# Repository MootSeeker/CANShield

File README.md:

# CANShield

STM32 Nucleo-64 Development Shield to connect NXP TJA1443 CANbus chip with some memory and GPS probe interface.

## Table of Contents
- [About](#about)
- [Features](#features)
- [Circuit Description](#circuit-description)
- [Hardware Requirements](#hardware-requirements)
- [Installation](#installation)
- [Usage](#usage)
- [Contributing](#contributing)
- [License](#license)
- [Contact](#contact)

## About
CANShield is a development shield designed for the STM32 Nucleo-64 board. It integrates an NXP TJA1443 CANbus transceiver, additional memory, and a GPS probe interface to facilitate the development and testing of CANbus applications. This shield provides a versatile and powerful platform for engineers and developers working on CANbus networks and applications, offering the tools needed to prototype and experiment with CAN-FD protocols.

## Features
- **Compatibility**: Fully compatible with STM32 Nucleo-64 boards, providing a seamless integration experience.
- **NXP TJA1443 CANbus Transceiver**: High-speed CAN-FD transceiver for robust and reliable CANbus communication.
- **Integrated Memory**: Additional memory for data storage, enabling complex applications and logging capabilities.
- **GPS Probe Interface**: Easy integration with GPS modules for applications requiring location data.
- **KiCad Design Files**: Open-source design files available, allowing for easy modifications and customizations.

## Circuit Description
This project includes the development and implementation of a custom development board with the NXP TJA1443 CAN-FD chip. The board connects to an Nucleo-64 development board, specifically the Nucleo-32G0B1, to fully exploit the capabilities of the CAN-FD interface.

The main purpose of this project is to utilize the full potential of the NXP TJA1443 chip in a CAN-FD network. By integrating this chip with the Nucleo-32G0B1, we aim to develop and test various protocols within the CAN network, providing a robust platform for CAN-FD communication.

Key Features:
- **NXP TJA1443 CAN-FD Chip**: High-speed CAN transceiver with advanced features for CAN-FD networks.
- **Nucleo-32G0B1 Compatibility**: Utilizes the STM32G0 microcontroller with integrated CAN-FD support.
- **Custom Development Board**: Tailored design for easy integration and testing of CAN-FD protocols.
- **Protocol Development and Testing**: Focus on creating and evaluating various protocols within the CAN network.

This project provides a comprehensive platform for developing and testing CAN-FD protocols, leveraging the capabilities of the NXP TJA1443 chip and the Nucleo-32G0B1 development board.

## Hardware Requirements
To get started with CANShield, you will need the following hardware components:
- **STM32 Nucleo-64 Board**: The main development board that hosts the STM32 microcontroller.
- **CANShield Board**: The custom shield that integrates the NXP TJA1443 CAN-FD transceiver, memory, and GPS interface.
- **GPS Probe (Optional)**: A GPS module for applications requiring geographic data.
- **Power Supply**: Appropriate power supply to power the Nucleo-64 and CANShield boards.

## Installation
1. **Clone the Repository**: Start by cloning the CANShield repository to your local machine.
    ```sh
    git clone https://github.com/MootSeeker/CANShield.git
    ```
2. **Open KiCad Project**: Open the KiCad project files located in the `CANShield` directory to review the schematics and PCB layout.
3. **Assemble the Shield**: Assemble the CANShield board according to the provided schematics and Bill of Materials (BOM). Ensure all components are correctly soldered and connected.
4. **Attach to Nucleo-64**: Connect the assembled CANShield board to the STM32 Nucleo-64 board.

## Usage
1. **Setup Hardware**: Attach the CANShield to the STM32 Nucleo-64 board. Connect the GPS probe to the shield if needed.
2. **Power Up**: Supply power to the setup using an appropriate power source.
3. **Program the STM32**: Upload your CANbus application code to the STM32 microcontroller using your preferred development environment (e.g., STM32CubeIDE).
4. **Monitor Communication**: Use CANbus monitoring tools to observe and debug the communication on the CANbus network. This can be done using software tools or hardware analyzers.

## Contributing
Contributions are welcome! Whether you have suggestions for improvements, bug fixes, or new features, please feel free to contribute. Here’s how you can get involved:
- **Open an Issue**: Report bugs or suggest features by opening an issue on the GitHub repository.
- **Submit a Pull Request**: Fork the repository, make your changes, and submit a pull request for review.
- **Documentation**: Help improve the project documentation by adding examples, tutorials, or clarifications.

## License
This project is licensed under the MIT License. You are free to use, modify, and distribute this project as per the terms of the license. See the [LICENSE](LICENSE) file for more details.

## Contact
For questions, feedback, or more information, please contact [MootSeeker](https://github.com/MootSeeker). We look forward to hearing from you and seeing how you use CANShield in your projects!

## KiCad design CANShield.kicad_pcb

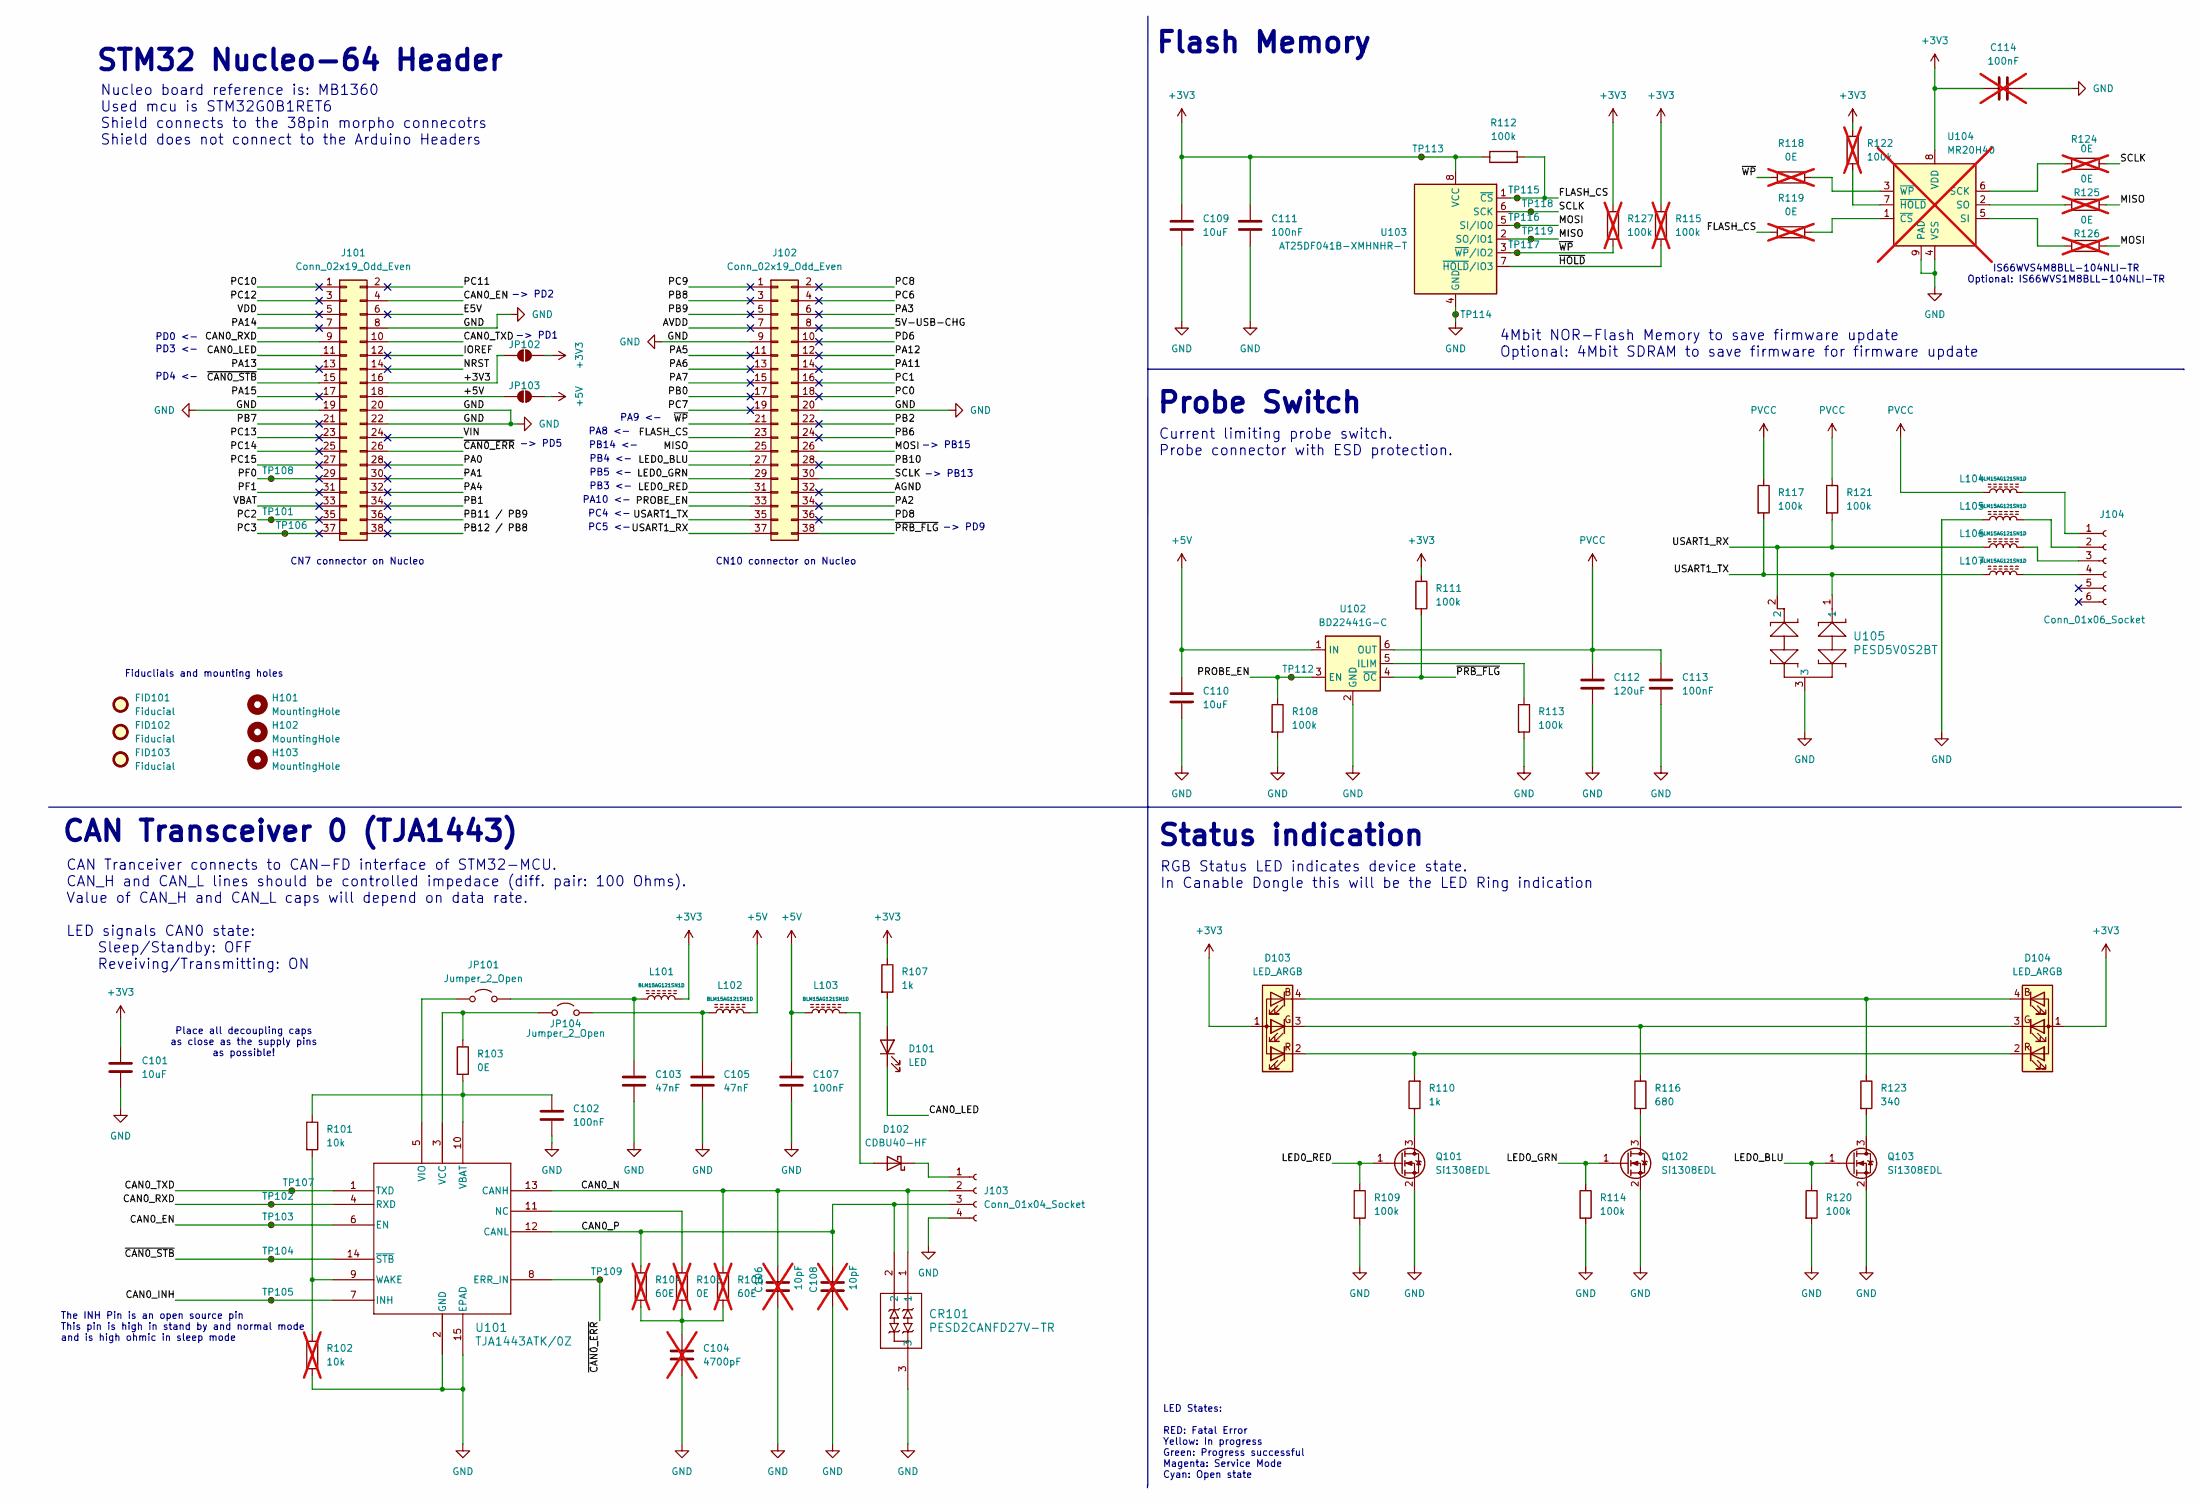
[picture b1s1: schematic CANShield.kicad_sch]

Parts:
C101, C109, C110: 10uF; C_0603_1608Metric_Pad1.08x0.95mm_HandSolder; JLCPCB Part # (optional) ${ITEM_NUMBER}
C102, C107, C111, C113: 100nF; C_0402_1005Metric_Pad0.74x0.62mm_HandSolder; JLCPCB Part # (optional) ${ITEM_NUMBER}
C103, C105: 47nF; C_0402_1005Metric_Pad0.74x0.62mm_HandSolder; JLCPCB Part # (optional) ${ITEM_NUMBER}
C104: 4700pF; C_0402_1005Metric_Pad0.74x0.62mm_HandSolder; JLCPCB Part # (optional) ${ITEM_NUMBER}; not fitted
C106, C108: 10pF; C_0402_1005Metric_Pad0.74x0.62mm_HandSolder; JLCPCB Part # (optional) ${ITEM_NUMBER}; not fitted
C112: 120uF; C_0603_1608Metric_Pad1.08x0.95mm_HandSolder; JLCPCB Part # (optional) ${ITEM_NUMBER}
C114: 100nF; C_0402_1005Metric_Pad0.74x0.62mm_HandSolder; JLCPCB Part # (optional) ${ITEM_NUMBER}; not fitted
CR101: PESD2CANFD27V-TR; SOT23_PESD2_NEX; JLCPCB Part # (optional) ${ITEM_NUMBER}
D101: LED; LED_0402_1005Metric_Pad0.77x0.64mm_HandSolder; JLCPCB Part # (optional) ${ITEM_NUMBER}
D102: CDBU40-HF; D_0603_1608Metric; JLCPCB Part # (optional) ${ITEM_NUMBER}
D103, D104: LED_ARGB; LED_155124M173200; JLCPCB Part # (optional) ${ITEM_NUMBER}
FID101, FID102, FID103: Fiducial; Fiducial_0.75mm_Mask2.25mm; JLCPCB Part # (optional) ${ITEM_NUMBER}
H101, H102, H103: MountingHole; MountingHole_2.7mm_M2.5; JLCPCB Part # (optional) ${ITEM_NUMBER}
J101, J102: Conn_02x19_Odd_Even; PinSocket_2x19_P2.54mm_Vertical; JLCPCB Part # (optional) ${ITEM_NUMBER}
J103: Conn_01x04_Socket; PinHeader_1x04_P2.54mm_Horizontal; JLCPCB Part # (optional) ${ITEM_NUMBER}
J104: Conn_01x06_Socket; Molex_PicoBlade_53048-0610_1x06_P1.25mm_Horizontal; JLCPCB Part # (optional) ${ITEM_NUMBER}
JP101, JP104: Jumper_2_Open; PinHeader_1x02_P2.54mm_Vertical; JLCPCB Part # (optional) ${ITEM_NUMBER}
JP102, JP103: SolderJumper_2_Open; PinHeader_1x02_P2.54mm_Vertical; JLCPCB Part # (optional) ${ITEM_NUMBER}
L101, L102, L103, L104, L105, L106, L107: BLM15AG121SN1D; L_0402_1005Metric_Pad0.77x0.64mm_HandSolder; JLCPCB Part # (optional) ${ITEM_NUMBER}
Q101, Q102, Q103: Si1308EDL; SOT-323_SC-70; JLCPCB Part # (optional) ${ITEM_NUMBER}
R101: 10k; R_0402_1005Metric_Pad0.72x0.64mm_HandSolder; JLCPCB Part # (optional) ${ITEM_NUMBER}
R102: 10k; R_0402_1005Metric_Pad0.72x0.64mm_HandSolder; JLCPCB Part # (optional) ${ITEM_NUMBER}; not fitted
R103: 0E; R_0402_1005Metric_Pad0.72x0.64mm_HandSolder; JLCPCB Part # (optional) ${ITEM_NUMBER}
R104, R106: 60E; R_0603_1608Metric_Pad0.98x0.95mm_HandSolder; JLCPCB Part # (optional) ${ITEM_NUMBER}; not fitted
R105: 0E; R_0603_1608Metric_Pad0.98x0.95mm_HandSolder; JLCPCB Part # (optional) ${ITEM_NUMBER}; not fitted
R107, R110: 1k; R_0402_1005Metric_Pad0.72x0.64mm_HandSolder; JLCPCB Part # (optional) ${ITEM_NUMBER}
R108, R109, R111, R112, R113, R114, R117, R120, R121: 100k; R_0402_1005Metric_Pad0.72x0.64mm_HandSolder; JLCPCB Part # (optional) ${ITEM_NUMBER}
R115, R122, R127: 100k; R_0402_1005Metric_Pad0.72x0.64mm_HandSolder; JLCPCB Part # (optional) ${ITEM_NUMBER}; not fitted
R116: 680; R_0402_1005Metric_Pad0.72x0.64mm_HandSolder; JLCPCB Part # (optional) ${ITEM_NUMBER}
R118, R119, R124, R125, R126: 0E; R_0402_1005Metric_Pad0.72x0.64mm_HandSolder; JLCPCB Part # (optional) ${ITEM_NUMBER}; not fitted
R123: 340; R_0402_1005Metric_Pad0.72x0.64mm_HandSolder; JLCPCB Part # (optional) ${ITEM_NUMBER}
TP101, TP102, TP103, TP104, TP105, TP106, TP107, TP108, TP109, TP112, TP113, TP114, TP115, TP116, TP117, TP118, TP119: TestPoint_Small; TestPoint_Pad_D1.0mm; JLCPCB Part # (optional) ${ITEM_NUMBER}
U101: TJA1443ATK/0Z; HVSON14_SOT1086-2_NXP; JLCPCB Part # (optional) ${ITEM_NUMBER}
U102: BD22441G-C; TSOP-6_1.65x3.05mm_P0.95mm; JLCPCB Part # (optional) C5576416
U103: AT25DF041B-XMHNHR-T; TSSOP-8_4.4x3mm_P0.65mm; JLCPCB Part # (optional) ${ITEM_NUMBER}
U104: MR20H40; SOIC-8-1EP_3.9x4.9mm_P1.27mm_EP2.29x3mm; JLCPCB Part # (optional) ${ITEM_NUMBER}; not fitted
U105: PESD5V0S2BT; SOT23_NEX

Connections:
+3V3: C101.1, C109.1, C111.1, C114.1, D103.1 (A), D104.1 (A), J101.16, JP102.1 (A), JP102.2 (B), L101.2, R107.1, R111.1, R112.1, R115.1, R122.2, R127.1, TP113.1, U103.8 (VCC), U104.8 (VDD)
+5V: C107.1, C110.1, J101.18, JP103.1 (A), JP103.2 (B), L102.2, L103.1, U102.1 (IN)
/5V-USB-CHG: J102.8
/AGND: J102.32
/AVDD: J102.7
/CAN0_EN: J101.4, TP103.1, U101.6 (EN)
/CAN0_INH: TP105.1, U101.7 (INH)
/CAN0_LED: D101.1 (K), J101.11
/CAN0_N: C106.1, CR101.1, J103.2, R106.1, U101.13 (CANH)
/CAN0_P: C108.1, CR101.2, J103.3, R104.1, U101.12 (CANL)
/CAN0_RXD: J101.9, TP102.1, U101.4 (RXD)
/CAN0_TXD: J101.10, TP107.1, U101.1 (TXD)
/E5V: J101.6
/FLASH_CS: J102.23, R112.2, R119.1, TP115.1, U103.1 (~CS)
/IOREF: J101.12
/LED0_BLU: J102.27, Q103.1 (G), R120.1
/LED0_GRN: J102.29, Q102.1 (G), R114.1
/LED0_RED: J102.31, Q101.1 (G), R109.1
/MISO: J102.25, R125.1, TP119.1, U103.2 (SO/IO1)
/MOSI: J102.26, R126.1, TP116.1, U103.5 (SI/IO0)
/NRST: J101.14
/PA0: J101.28
/PA1: J101.30
/PA2: J102.34
/PA3: J102.6
/PA4: J101.32
/PA5: J102.11
/PA6: J102.13
/PA7: J102.15
/PA11: J102.14
/PA12: J102.12
/PA13: J101.13
/PA14: J101.7
/PA15: J101.17
/PB0: J102.17
/PB1: J101.34
/PB2: J102.22
/PB6: J102.24
/PB7: J101.21
/PB8: J102.3
/PB9: J102.5
/PB10: J102.28
/PB11 / PB9: J101.36
/PB12 / PB8: J101.38
/PC0: J102.18
/PC1: J102.16
/PC2: J101.35, TP101.1
/PC3: J101.37, TP106.1
/PC6: J102.4
/PC7: J102.19
/PC8: J102.2
/PC9: J102.1
/PC10: J101.1
/PC11: J101.2
/PC12: J101.3
/PC13: J101.23
/PC14: J101.25
/PC15: J101.27
/PD6: J102.10
/PD8: J102.36
/PF0: J101.29, TP108.1
/PF1: J101.31
/PROBE_EN: J102.33, R108.1, TP112.1, U102.3 (EN)
/SCLK: J102.30, R124.1, TP118.1, U103.6 (SCK)
/USART1_RX: J102.37, L106.1, R121.2, U105.2
/USART1_TX: J102.35, L107.1, R117.2, U105.1
/VBAT: J101.33
/VDD: J101.5
/VIN: J101.24
/~CAN0_ERR: J101.26, TP109.1, U101.8 (ERR_IN)
/~CAN0_STB: J101.15, TP104.1, U101.14 (~STB)
/~HOLD: R115.2, U103.7 (~HOLD/IO3)
/~PRB_FLG: J102.38, R111.2, U102.4 (~OC)
/~WP: J102.21, R118.1, R127.2, TP117.1, U103.3 (~WP/IO2)
GND: C101.2, C102.2, C103.2, C104.2, C105.2, C106.2, C107.2, C108.2, C109.2, C110.2, C111.2, C112.2, C113.2, C114.2, CR101.3, J101.8, J101.19, J101.20, J101.22, J102.9, J102.20, J103.4, L105.1, Q101.2 (S), Q102.2 (S), Q103.2 (S), R102.2, R108.2, R109.2, R113.2, R114.2, R120.2, TP114.1, U101.2 (GND), U101.15 (EPAD), U102.2 (GND), U103.4 (GND), U104.4 (VSS), U104.9 (PAD), U105.3
unnamed: C104.1, R104.2, R105.1, R106.2
unnamed: D101.2 (A), R107.2
unnamed: D102.2 (A), L103.2
unnamed: D102.1 (K), J103.1
unnamed: D103.4 (BK), D104.4 (BK), R123.1
unnamed: D103.3 (GK), D104.3 (GK), R116.1
unnamed: D103.2 (RK), D104.2 (RK), R110.2
unnamed: J104.1, L104.2
unnamed: J104.2, L105.2
unnamed: J104.3, L106.2
unnamed: J104.4, L107.2
unnamed: JP101.1 (A), U101.5 (VIO)
unnamed: C103.1, JP101.2 (B), L101.1
unnamed: JP104.1 (A), R103.1, U101.3 (VCC)
unnamed: C105.1, JP104.2 (B), L102.1
unnamed: Q101.3 (D), R110.1
unnamed: Q102.3 (D), R116.2
unnamed: Q103.3 (D), R123.2
unnamed: R105.2, U101.11 (NC)
unnamed: C102.1, R101.1, R103.2, U101.10 (VBAT)
unnamed: R101.2, R102.1, U101.9 (WAKE)
unnamed: R113.1, U102.5 (ILIM)
unnamed: R124.2, U104.6 (SCK)
unnamed: R126.2, U104.5 (SI)
unnamed: R125.2, U104.2 (SO)
unnamed: R119.2, U104.1 (~CS)
unnamed: R122.1, U104.7 (~HOLD)
unnamed: R118.2, U104.3 (~WP)
PVCC: C112.1, C113.1, L104.1, R117.1, R121.1, U102.6 (OUT)

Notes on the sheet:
CAN Transceiver 0 (TJA1443)
CN7 connector on Nucleo
PD4 <-
RGB Status LED indicates device state. In Canable Dongle this will be the LED Ring indication
-> PD1
PB5 <-
PA9 <-
PB4 <-
The INH Pin is an open source pin This pin is high in stand by and normal mode and is high ohmic in sleep mode
IS66WVS4M8BLL-104NLI-TR Optional: IS66WVS1M8BLL-104NLI-TR
PC5 <-
STM32 Nucleo-64 Header
Nucleo board reference is: MB1360 Used mcu is STM32G0B1RET6 Shield connects to the 38pin morpho connecotrs Shield does not connect to the Arduino Headers
Place all decoupling caps as close as the supply pins as possible!
Status indication
PB3 <-
Probe Switch
CN10 connector on Nucleo
PA8 <-
-> PB15
CAN Tranceiver connects to CAN-FD interface of STM32-MCU. CAN_H and CAN_L lines should be controlled impedace (diff. pair: 100 Ohms). Value of CAN_H and CAN_L caps will depend on data rate. LED signals CAN0 state: Sleep/Standby: OFF Reveiving/Transmitting: ON
-> PD9
-> PD5
4Mbit NOR-Flash Memory to save firmware update Optional: 4Mbit SDRAM to save firmware for firmware update
Current limiting probe switch. Probe connector with ESD protection.
PD0 <-
PB14 <-
-> PB13
PC4 <-
Flash Memory
LED States: RED: Fatal Error Yellow: In progress Green: Progress successful Magenta: Service Mode Cyan: Open state
Fiduclials and mounting holes
-> PD2
PD3 <-
PA10 <-

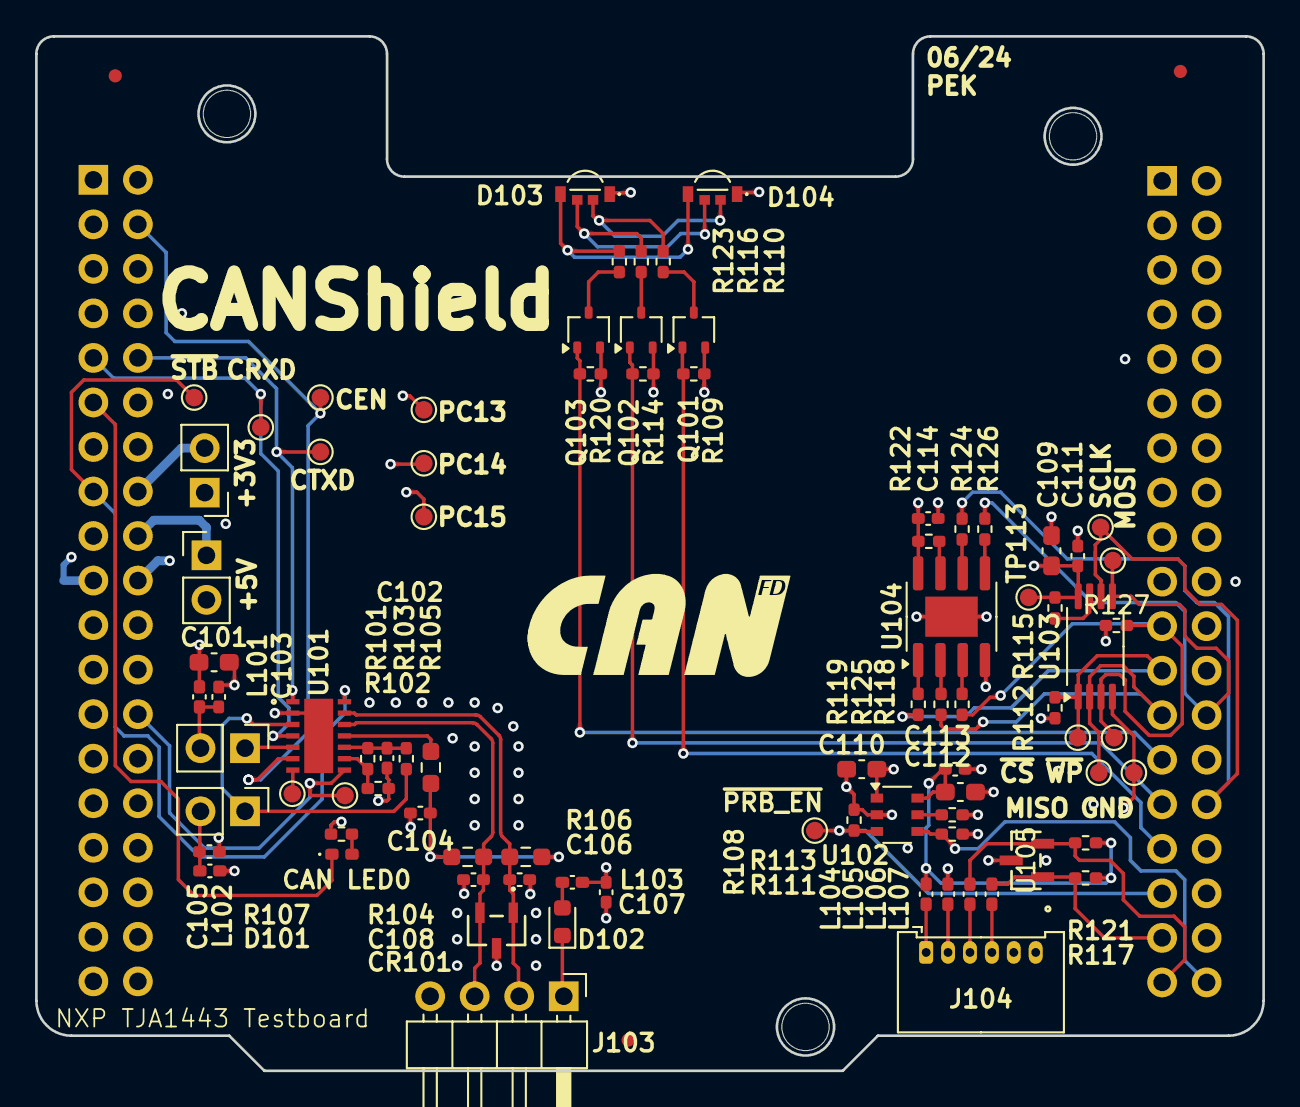
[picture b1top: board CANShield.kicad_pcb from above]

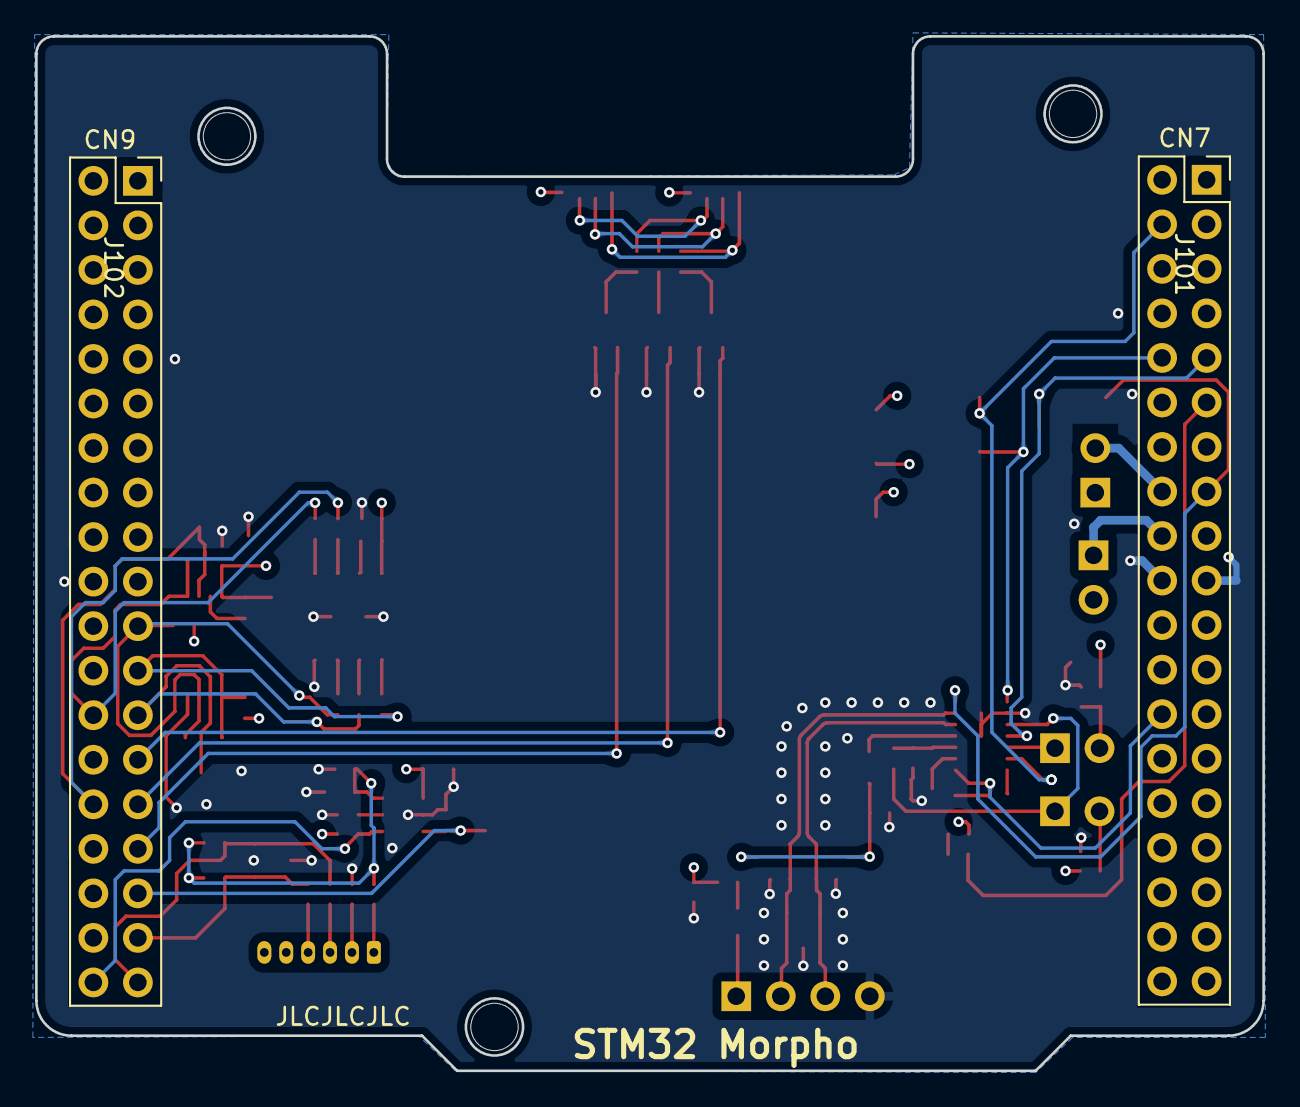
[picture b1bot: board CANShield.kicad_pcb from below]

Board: 4 copper layers, 70.0 x 59.0 mm, 91 parts (2 on the bottom side), 57 nets.

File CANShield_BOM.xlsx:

Comment | Designator | Footprint | JLCPCB Part # (optional)
10uF | C101,C109,C110 | Capacitor_SMD:C_0603_1608Metric_Pad1.08x0.95mm_HandSolder | C96446
100nF | C102,C107,C111,C113,C114 | Capacitor_SMD:C_0402_1005Metric_Pad0.74x0.62mm_HandSolder | C307331
47nF | C103,C105 | Capacitor_SMD:C_0402_1005Metric_Pad0.74x0.62mm_HandSolder | C1622
4700pF | C104 | Capacitor_SMD:C_0402_1005Metric_Pad0.74x0.62mm_HandSolder | C1538
10pF | C106,C108 | Capacitor_SMD:C_0402_1005Metric_Pad0.74x0.62mm_HandSolder | C32949
120uF | C112 | Capacitor_SMD:C_0603_1608Metric_Pad1.08x0.95mm_HandSolder | C2835554
PESD2CANFD27V-TR | CR101,CR102 | PESD2CANFD27V-TR:SOT23_PESD2_NEX | C552488
LED | D101 | LED_SMD:LED_0402_1005Metric_Pad0.77x0.64mm_HandSolder | C2856703
CDBU40-HF | D102 | Diode_SMD:D_0603_1608Metric | C3012735
LED_ARGB | D103,D104 | 155124M173200:LED_155124M173200
BLM15AG121SN1D | L101,L102,L103,L104,L105,L106,L107 | Inductor_SMD:L_0402_1005Metric_Pad0.77x0.64mm_HandSolder | C85812
Si1308EDL | Q101,Q102,Q103 | Package_TO_SOT_SMD:SOT-323_SC-70 | C469327
10k | R101, R102 | Resistor_SMD:R_0402_1005Metric_Pad0.72x0.64mm_HandSolder | C25744
0E | R103,R105,R118,R119,R124,R125,R126 | Resistor_SMD:R_0402_1005Metric_Pad0.72x0.64mm_HandSolder | C472872
60E | R104, R106 | Resistor_SMD:R_0603_1608Metric_Pad0.98x0.95mm_HandSolder | C911580
1k | R107,R110,R116,R123 | Resistor_SMD:R_0402_1005Metric_Pad0.72x0.64mm_HandSolder | C2763771
100k | R108,R109,R111,R112,R113,R114,R115,R117,R120,R121. R122 | Resistor_SMD:R_0402_1005Metric_Pad0.72x0.64mm_HandSolder | C427222
TJA1443ATK/0Z | U101 | TJA1443ATK:HVSON14_SOT1086-2_NXP | C5202327
BD2222G | U102 | Package_SO:TSOP-6_1.65x3.05mm_P0.95mm | C559606
AT25SF081-XMHD-X | U103 | Package_SO:TSSOP-8_4.4x3mm_P0.65mm | C2061730
MR20H40 | U104 | Package_SO:SOIC-8-1EP_3.9x4.9mm_P1.27mm_EP2.29x3mm | C19308182

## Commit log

2024-06-19 Add project
2024-06-19 Moved files one folder up
2024-06-19 Save schematics
2024-06-20 Add NXP TJA1443 CAN-FD Chip
    Add reference design for CAN-FD chip
2024-06-20 Update CANShield.kicad_sch
    Add complete Nucleo Pinout
2024-06-20 Update CANShield.kicad_sch
    Add testpoints and documentation
2024-06-21 Update CANShield.kicad_sch
    Add probe connector and Flash memory
2024-06-22 Add PCB
    started design
2024-06-23 pcb in progress
    working on pcb layout
2024-06-23 working on PCB
2024-06-24 finished PCB
2024-06-24 Add BOM to project
    Add BOM and did Gerber Data
2024-06-24 update BOM
2024-06-25 Update BOM
    Small changes on pcb layout and update BOM
2024-06-25 Update README.md
    translated into english
2024-06-27 Add bew esd diode
2024-06-27 Moved Testpoints
2024-06-29 changes from pcb review
    update pcb with remained changes in pcb review.
2024-06-29 Update CANShield.kicad_pcb
    all changes from review. PCB ready for final review.
